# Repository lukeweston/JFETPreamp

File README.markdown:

JFETPreamp 

This board does not include a high voltage bias tee - the bias tee and blocking capacitor needs to be before the signal reaches this board, with no HV component!
To get the desired 0-10V output from the amplifier there will need to be a 10V supply voltage, but a smaller supply voltage of say 5V is acceptable if the desired output amplitude is sufficiently small.

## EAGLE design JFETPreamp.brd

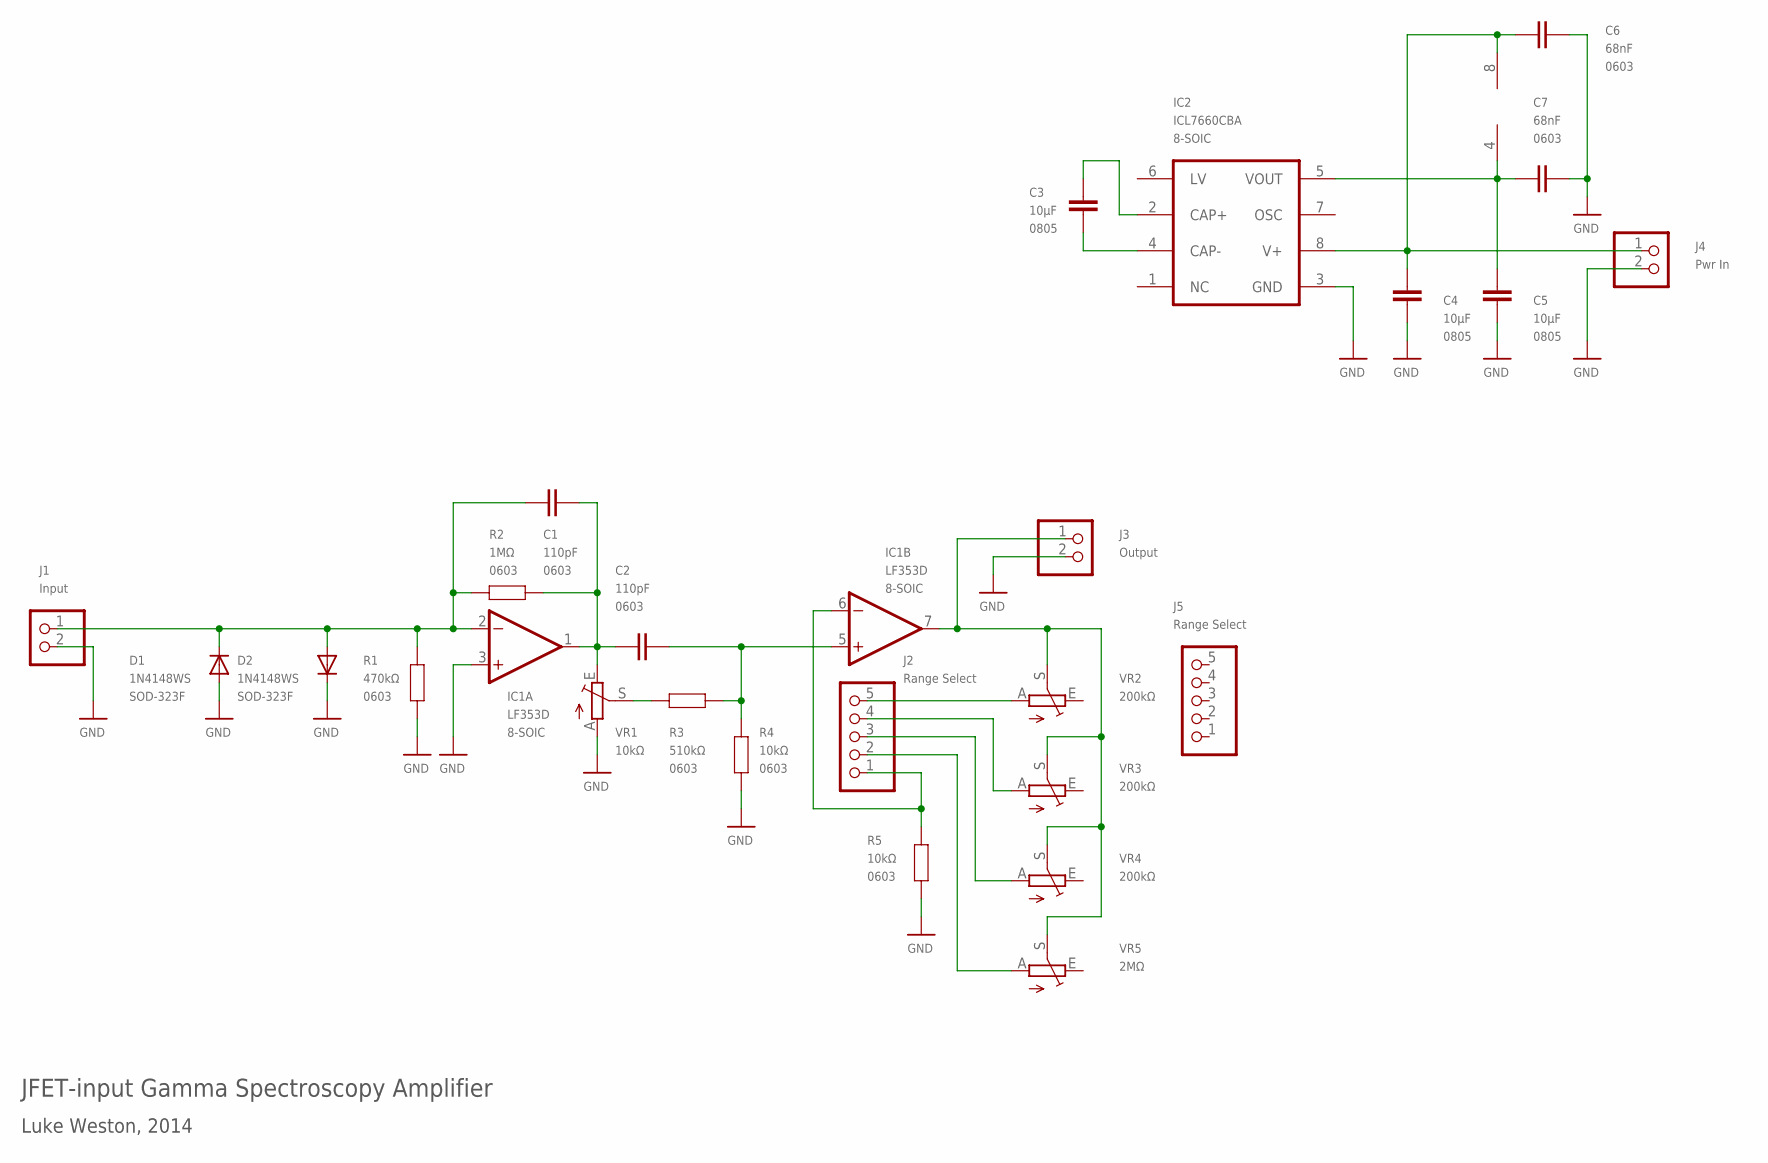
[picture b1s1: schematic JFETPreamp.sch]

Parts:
C1, C2: 110pF; 0603
C3, C4, C5: 10µF; C0805K
C6, C7: 68nF; 0603
D1, D2: 1N4148WS; SOD-323
IC1: LF353D; SO08
IC2: ICL7660CBA; SO08
J1: Input; 1X02
J2, J5: Range Select; 1X05
J3: Output; 1X02
J4: Pwr In; 1X02
R1: 470kΩ; 0603
R2: 1MΩ; 0603
R3: 510kΩ; 0603
R4, R5: 10kΩ; 0603
VR1: 10kΩ; B25P
VR2, VR3, VR4: 200kΩ; B25P
VR5: 2MΩ; B25P

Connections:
GND: C4.2, C5.2, C6.1, C7.1, D1.2 (A), D2.1 (C), IC1.3 (+IN), IC2.3 (GND), J1.2, J3.2, J4.2, R1.1, R4.2, R5.2, VR1.A
unnamed: C1.1, D1.1 (C), D2.2 (A), IC1.2 (-IN), J1.1, R1.2, R2.2
unnamed: C2.2, IC1.5 (+IN), R3.1, R4.1
unnamed: C1.2, C2.1, IC1.1 (OUT), R2.1, VR1.E
unnamed: IC1.6 (-IN), J2.1, R5.1
unnamed: R3.2, VR1.S
unnamed: J2.5, VR2.A
unnamed: IC1.7 (OUT), J3.1, VR2.S, VR3.S, VR4.S, VR5.S
unnamed: J2.4, VR3.A
unnamed: J2.3, VR4.A
unnamed: J2.2, VR5.A
unnamed: C5.1, C7.2, IC1.4 (V-), IC2.5 (VOUT)
unnamed: C4.1, C6.2, IC1.8 (V+), IC2.8 (V+), J4.1
unnamed: C3.1, IC2.2 (CAP+)
unnamed: C3.2, IC2.4 (CAP-)

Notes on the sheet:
JFET-input Gamma Spectroscopy Amplifier
Luke Weston, 2014

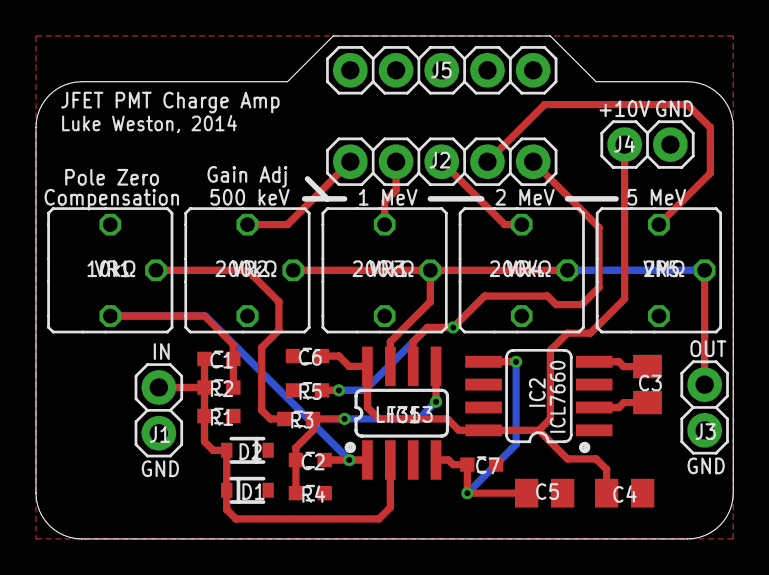
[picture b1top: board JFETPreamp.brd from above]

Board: 2 copper layers, 38.7 x 27.9 mm, 26 parts (0 on the bottom side), 15 nets.

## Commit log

2014-04-14 tweaked readme
2014-04-15 tweaked silkscreen
2014-04-20 changed to single dual opamp
2014-05-06 changed selector switch footprint
